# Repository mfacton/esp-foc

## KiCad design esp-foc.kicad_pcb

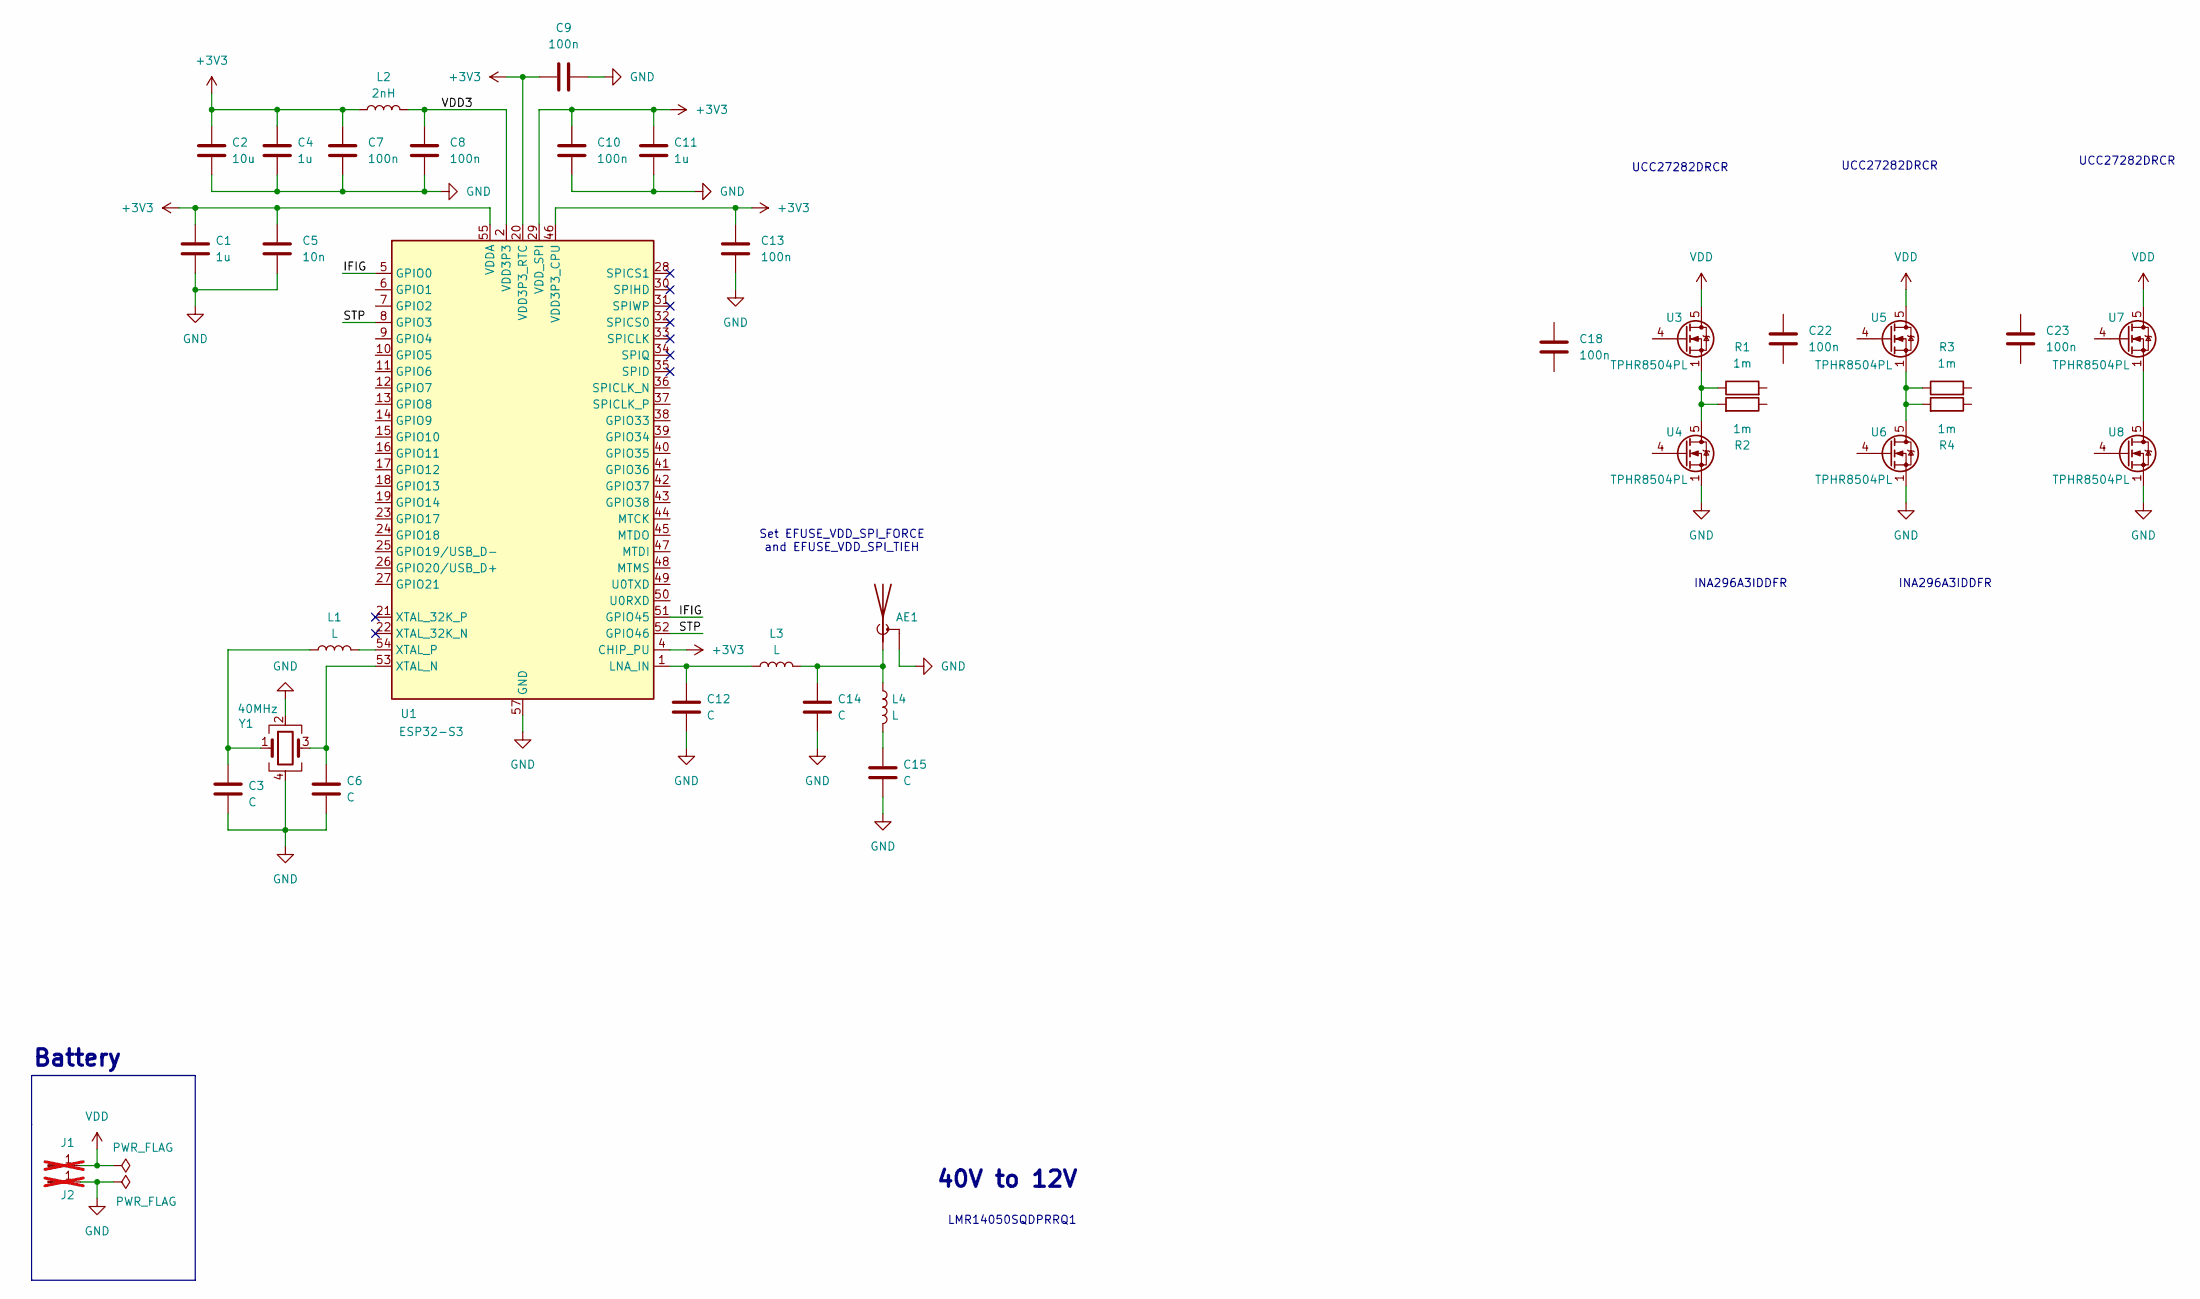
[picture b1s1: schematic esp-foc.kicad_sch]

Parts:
AE1: Antenna_Shield; U.FL_Molex_MCRF_73412-0110_Vertical; LCSC C434806
C1, C4, C11: 1u; C_0402_1005Metric; LCSC C52923
C2: 10u; C_0402_1005Metric; LCSC C15525
C3, C6: C; R_0402_1005Metric
C5: 10n; C_0402_1005Metric
C7, C8, C9, C10, C13: 100n; C_0402_1005Metric; LCSC C1525
C12, C14, C15: C; C_0402_1005Metric
C18, C22, C23: 100n; C_0402_1005Metric
J1, J2: Conn_01x01_Pin; MountingHole_3.2mm_M3_Pad_Via; not fitted
L1, L3, L4: L; L_0402_1005Metric
L2: 2nH; L_0402_1005Metric; LCSC C18216
R1, R2, R3, R4: 1m; R_1206_3216Metric; LCSC C18724164
U1: ESP32-S3; QFN-56-1EP_7x7mm_P0.4mm_EP4x4mm; LCSC C3013940
U3, U4, U5, U6, U7, U8: TPHR8504PL; PQFN-8-EP_6x5mm_P1.27mm_Generic; LCSC C22388172
Y1: 40MHz; Crystal_SMD_2520-4Pin_2.5x2.0mm; LCSC C2885592

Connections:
+3V3: C1.1, C2.1, C4.1, C5.1, C7.1, C9.1, C10.1, C11.1, C13.1, L2.1, U1.4 (CHIP_PU), U1.20 (VDD3P3_RTC), U1.29 (VDD_SPI), U1.46 (VDD3P3_CPU), U1.55 (VDDA), U1.56 (VDDA)
/IFIG: U1.5 (GPIO0), U1.51 (GPIO45)
/STP: U1.8 (GPIO3), U1.52 (GPIO46)
/VDD3: C8.1, L2.2, U1.2 (VDD3P3), U1.3 (VDD3P3)
GND: AE1.2 (Shield), C1.2, C2.2, C3.2, C4.2, C5.2, C6.2, C7.2, C8.2, C9.2, C10.2, C11.2, C12.2, C13.2, C14.2, C15.2, J2.1, U1.57 (GND), U4.1 (S), U4.2 (S), U4.3 (S), U6.1 (S), U6.2 (S), U6.3 (S), U8.1 (S), U8.2 (S), U8.3 (S), Y1.2, Y1.4
unnamed: AE1.1 (A), C14.1, L3.2, L4.1
unnamed: C3.1, L1.1, Y1.1
unnamed: C15.1, L4.2
unnamed: C12.1, L3.1, U1.1 (LNA_IN)
unnamed: C6.1, U1.53 (XTAL_N), Y1.3
unnamed: L1.2, U1.54 (XTAL_P)
unnamed: R1.1, R2.2, U3.1 (S), U3.2 (S), U3.3 (S), U4.5 (D)
unnamed: R3.1, R4.2, U5.1 (S), U5.2 (S), U5.3 (S), U6.5 (D)
unnamed: U7.1 (S), U7.2 (S), U7.3 (S), U8.5 (D)
VDD: J1.1, U3.5 (D), U5.5 (D), U7.5 (D)

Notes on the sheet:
LMR14050SQDPRRQ1
40V to 12V
Set EFUSE_VDD_SPI_FORCE and EFUSE_VDD_SPI_TIEH
UCC27282DRCR
INA296A3IDDFR
Battery

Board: 4 copper layers, 38 parts (0 on the bottom side), 15 nets, no tracks yet.

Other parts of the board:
J2#2: Conn_01x01_Pin; MountingHole_3.2mm_M3_Pad_Via

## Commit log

2024-12-21 Save
